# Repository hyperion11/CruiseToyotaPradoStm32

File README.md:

# CruiseToyotaPradoStm32
Cruise control for toyota prado 95
Круиз контроль для TLC Prado 95

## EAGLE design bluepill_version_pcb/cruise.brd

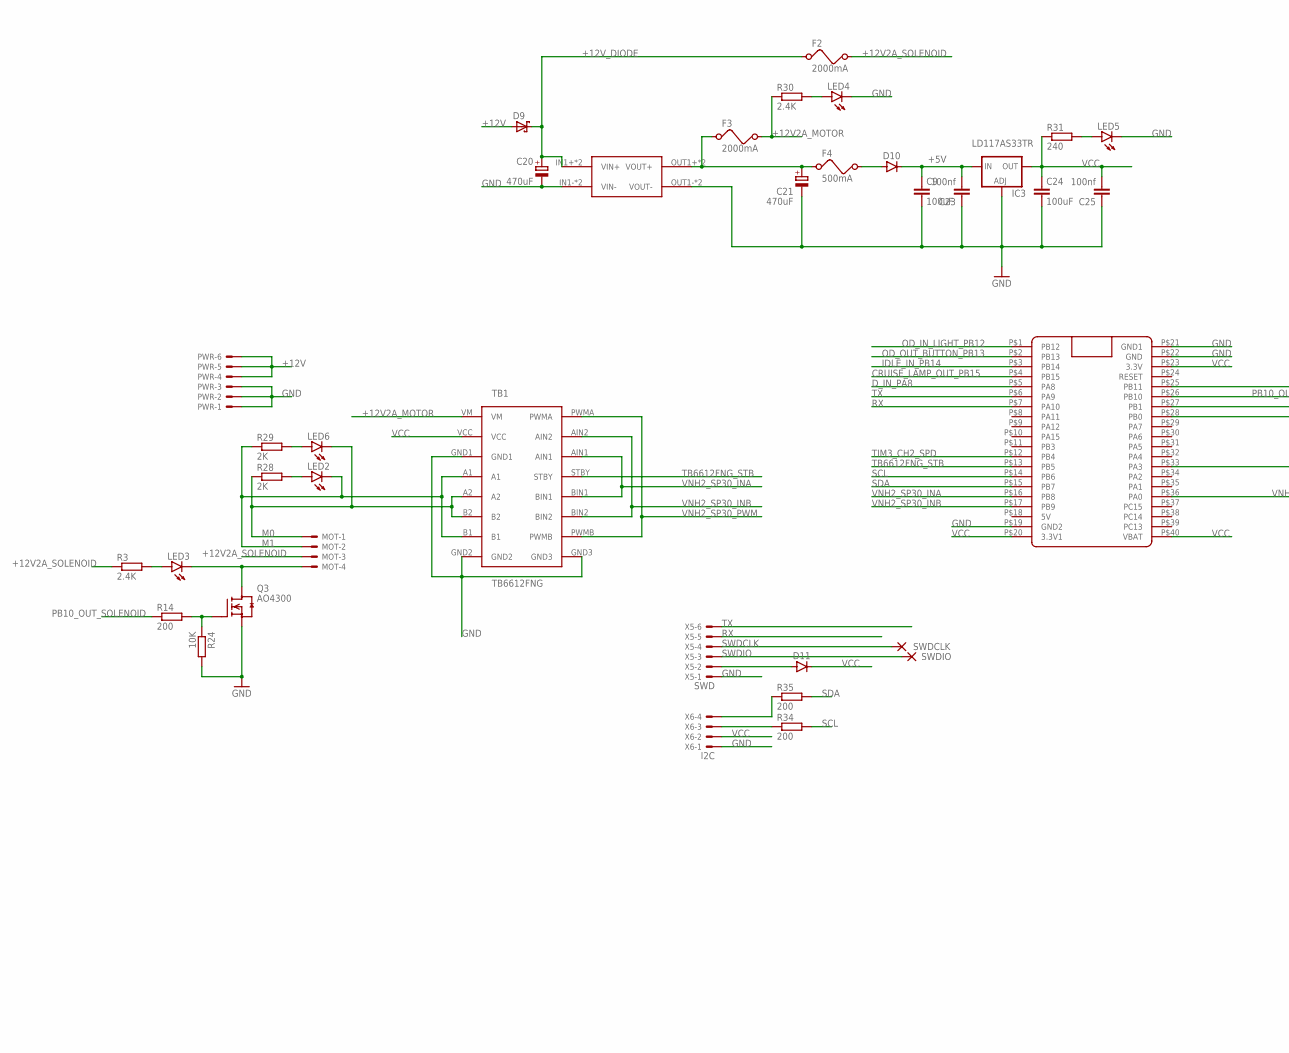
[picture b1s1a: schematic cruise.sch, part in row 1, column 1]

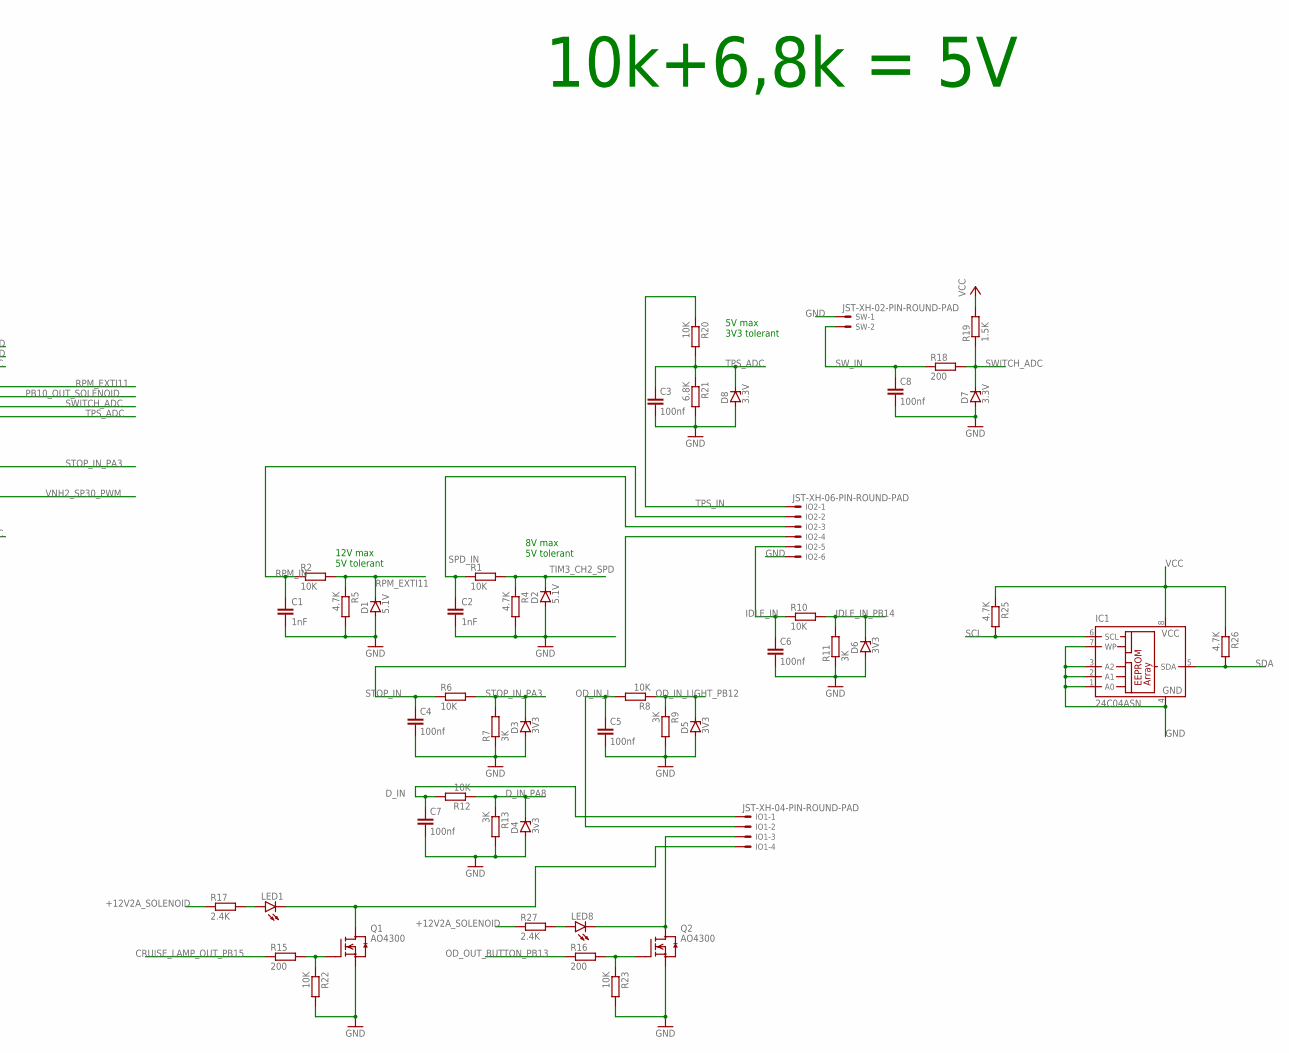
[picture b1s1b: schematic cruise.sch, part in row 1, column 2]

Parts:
C1, C2: 1nF; C0805K
C3, C4, C5, C6, C7, C8: 100nf; C0805K
C9, C24: 100uF; C1210
C20, C21: 470uF; PANASONIC_G
C23, C25: 100nf; C0805
D1, D2: 5.1V; SOD80C
D3, D5, D6: 3V3; SOD80C
D4: 3v3; SOD80C
D7, D8: 3.3V; SOD80C
D9: SCHOTTKY-DIODESMC; DIODE_SMC
D10, D11: DIODE-SOD323-W; SOD323-W
F2, F3: 2000mA; 1206
F4: 500mA; 1206
IC1: 24C04ASN; SO-08
IC3: LD117AS33TR; SOT223
IO1: JST-XH-04-PIN-ROUND-PAD; JST-XH-04-PACKAGE-ROUND-PAD
IO2: JST-XH-06-PIN-ROUND-PAD; JST-XH-06-PACKAGE-ROUND-PAD
LED1, LED2, LED3, LED4, LED5, LED6, LED8: LED3MM
MOT: JST-XH-04-PIN-LONG-PAD; JST-XH-04-PACKAGE-LONG-PAD
PWR: JST-XH-06-PIN-LONG-PAD; JST-XH-06-PACKAGE-LONG-PAD
Q1, Q2, Q3: AO4300; SOT23
R1, R2, R6, R8, R10, R12, R20, R22, R23, R24: 10K; R0805
R3, R17, R27, R30: 2.4K; R0805
R4, R5, R25, R26: 4.7K; R0805
R7, R9, R11, R13: 3K; R0805
R14, R15, R16, R18, R34, R35: 200; R0805
R19: 1.5K; R0805
R21: 6.8K; R0805
R28, R29: 2K; R0805
R31: 240; R0805
SW: JST-XH-02-PIN-ROUND-PAD; JST-XH-02-PACKAGE-ROUND-PAD
SWDCLK: WIREPAD2,15/1,0; 2,15/1,0
SWDIO: WIREPAD2,15/1,0; 2,15/1,0
TB1: TB6612FNG
U$1: BLUE_PILL
U$6: MP1584; DC-BRICK
X5: SWD; JST-XH-06-PACKAGE-ROUND-PAD
X6: I2C; JST-XH-04-PACKAGE-ROUND-PAD

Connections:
+5V: C9.1, C23.2, D10.C, IC3.3 (IN)
+12V: D9.A (C), PWR.4, PWR.5, PWR.6
+12V2A_MOTOR: F3.2, R30.1, TB1.VM
+12V2A_SOLENOID: F2.2, MOT.3, R3.1, R17.1, R27.1
+12V_DIODE: C20.+, D9.C (A), F2.1, U$6.IN1+ (VIN+), U$6.IN2+ (VIN+)
CRUISE_LAMP_OUT_PB15: R15.1, U$1.P$4 (PB15)
D_IN: C7.1, IO1.1, R12.2
D_IN_PA8: D4.C, R12.1, R13.1, U$1.P$5 (PA8)
GND: C1.2, C2.2, C3.2, C4.2, C5.2, C6.2, C7.2, C8.2, C9.2, C20.-, C21.-, C23.1, C24.2, C25.1, D1.A, D2.A, D3.A, D4.A, D5.A, D6.A, D7.A, D8.A, IC1.1 (A0), IC1.2 (A1), IC1.3 (A2), IC1.4 (GND), IC1.7 (WP), IC3.1 (ADJ), IO2.6, LED4.K (C), LED5.K (C), PWR.1, PWR.2, PWR.3, Q1.2 (S), Q2.2 (S), Q3.2 (S), R4.2, R5.2, R7.1, R9.2, R11.1, R13.2, R21.2, R22.2, R23.2, R24.2, SW.1, TB1.GND1, TB1.GND2, TB1.GND3, U$1.P$19 (GND2), U$1.P$21 (GND1), U$1.P$22 (GND), U$6.IN1- (VIN-), U$6.IN2- (VIN-), U$6.OUT1- (VOUT-), U$6.OUT2- (VOUT-), X5.1, X6.1
IDLE_IN: C6.1, IO2.5, R10.1
IDLE_IN_PB14: D6.C, R10.2, R11.2, U$1.P$3 (PB14)
M0: LED6.K (C), MOT.1, R28.1, TB1.A2, TB1.B2
M1: LED2.K (C), MOT.2, R29.1, TB1.A1, TB1.B1
unnamed: LED1.A, R17.2
unnamed: D10.A, F4.2
unnamed: D11.A, X5.2
unnamed: LED3.A, R3.2
unnamed: C21.+, F3.1, F4.1, U$6.OUT1+ (VOUT+), U$6.OUT2+ (VOUT+)
unnamed: LED3.K (C), MOT.4, Q3.3 (D)
unnamed: LED2.A, R28.2
unnamed: Q3.1 (G), R14.2, R24.1
unnamed: LED8.A, R27.2
unnamed: Q1.1 (G), R15.2, R22.1
unnamed: R34.1, X6.3
unnamed: R35.1, X6.4
unnamed: LED6.A, R29.2
unnamed: Q2.1 (G), R16.2, R23.1
unnamed: LED4.A, R30.2
unnamed: LED5.A, R31.2
unnamed: IO1.4, LED1.K (C), Q1.3 (D)
unnamed: IO1.3, LED8.K (C), Q2.3 (D)
OD_IN_L: C5.1, IO1.2, R8.2
OD_IN_LIGHT_PB12: D5.C, R8.1, R9.1, U$1.P$1 (PB12)
OD_OUT_BUTTON_PB13: R16.1, U$1.P$2 (PB13)
PB10_OUT_SOLENOID: R14.1, U$1.P$26 (PB10)
RPM_EXTI11: D1.C, R2.2, R5.1, U$1.P$25 (PB11)
RPM_IN: C1.1, IO2.2, R2.1
RX: U$1.P$7 (PA10), X5.5
SCL: IC1.6 (SCL), R25.2, R34.2, U$1.P$14 (PB6)
SDA: IC1.5 (SDA), R26.2, R35.2, U$1.P$15 (PB7)
SPD_IN: C2.1, IO2.3, R1.1
STOP_IN: C4.1, IO2.4, R6.1
STOP_IN_PA3: D3.C, R6.2, R7.2, U$1.P$33 (PA3)
SWDCLK: SWDCLK.1, X5.4
SWDIO: SWDIO.1, X5.3
SWITCH_ADC: D7.C, R18.2, R19.1, U$1.P$27 (PB1)
SW_IN: C8.1, R18.1, SW.2
TB6612FNG_STB: TB1.STBY, U$1.P$13 (PB5)
TIM3_CH2_SPD: D2.C, R1.2, R4.1, U$1.P$12 (PB4)
TPS_ADC: C3.1, D8.C, R20.2, R21.1, U$1.P$28 (PB0)
TPS_IN: IO2.1, R20.1
TX: U$1.P$6 (PA9), X5.6
VCC: C24.1, C25.2, D11.C, IC1.8 (VCC), IC3.4 (OUT), R19.2, R25.1, R26.1, R31.1, TB1.VCC, U$1.P$20 (3.3V1), U$1.P$23 (3.3V), U$1.P$40 (VBAT), X6.2
VNH2_SP30_INA: TB1.AIN1, TB1.BIN1, U$1.P$16 (PB8)
VNH2_SP30_INB: TB1.AIN2, TB1.BIN2, U$1.P$17 (PB9)
VNH2_SP30_PWM: TB1.PWMA, TB1.PWMB, U$1.P$36 (PA0)

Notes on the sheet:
10k+6,8k = 5V
8V max 5V tolerant
12V max 5V tolerant
5V max 3V3 tolerant

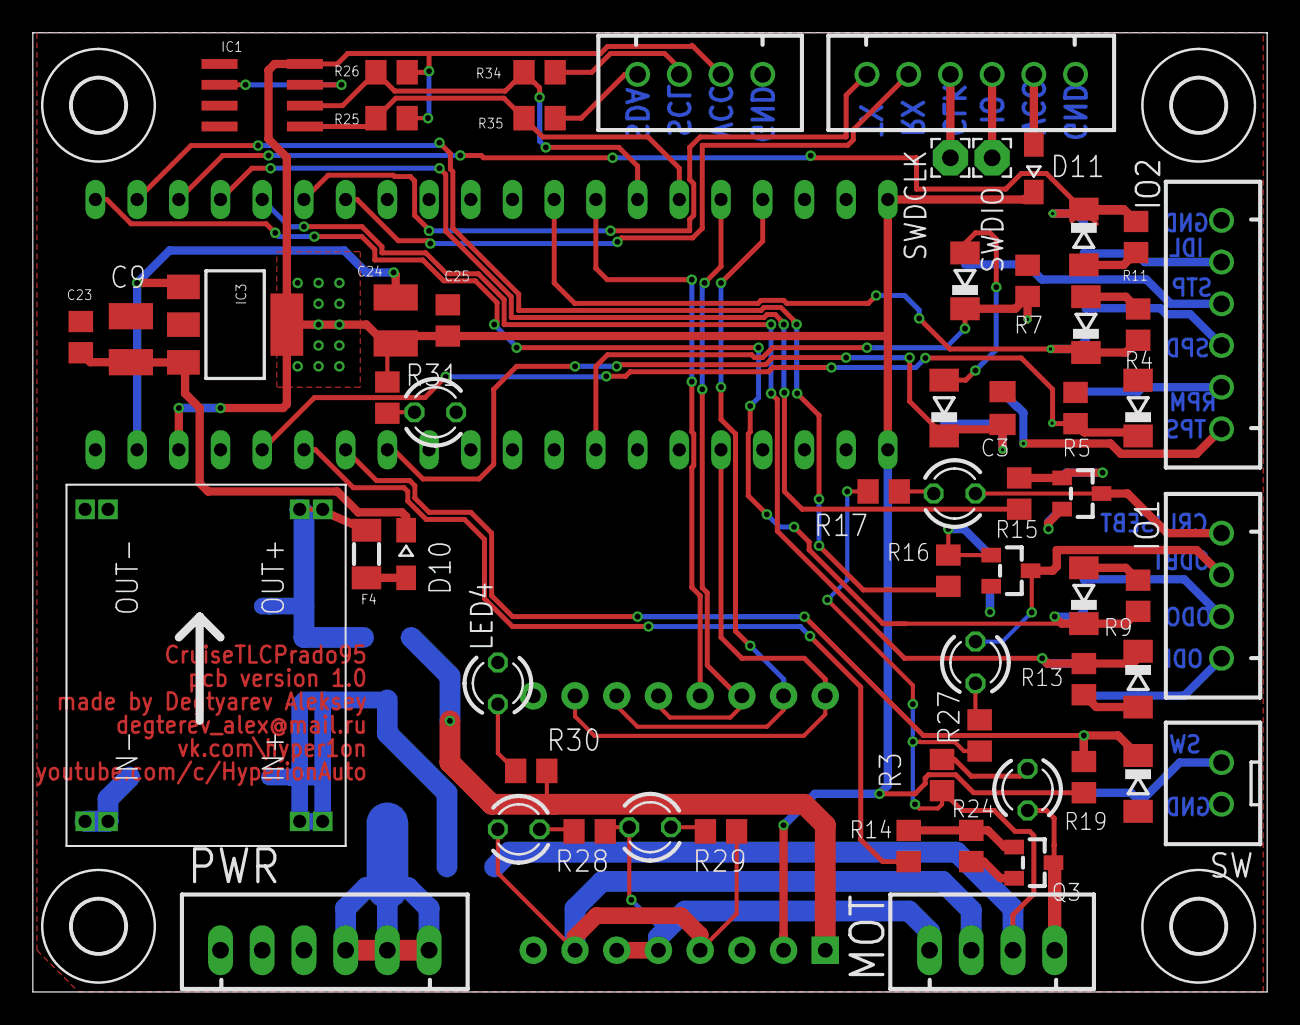
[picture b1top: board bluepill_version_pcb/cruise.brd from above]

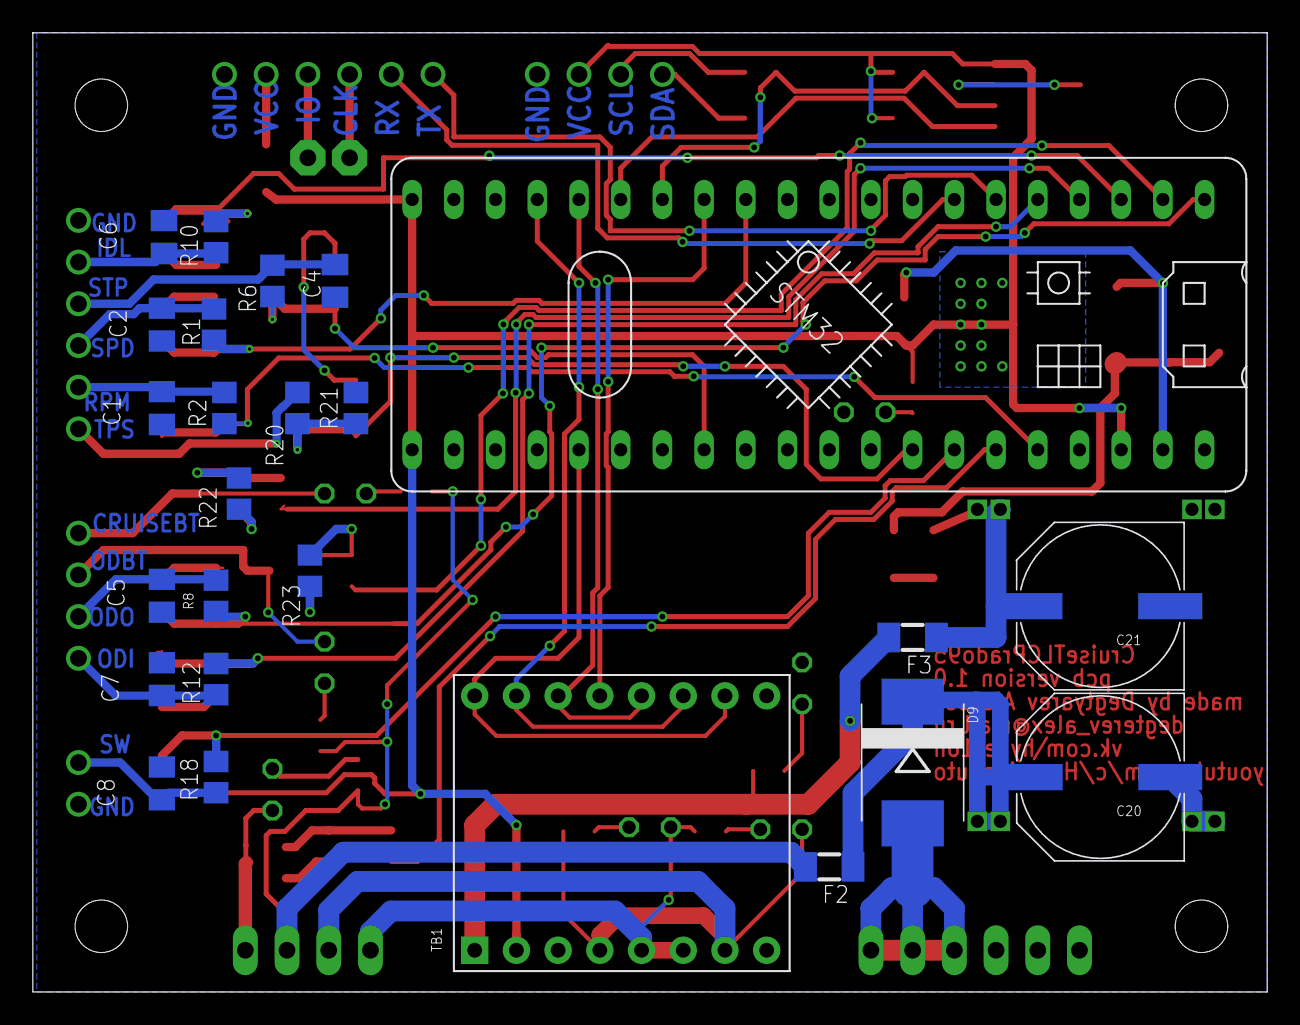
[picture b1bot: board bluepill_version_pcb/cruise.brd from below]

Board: 2 copper layers, 75.2 x 58.4 mm, 89 parts (25 on the bottom side), 56 nets.

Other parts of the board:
U$2, U$3, U$4, U$5: 3,2

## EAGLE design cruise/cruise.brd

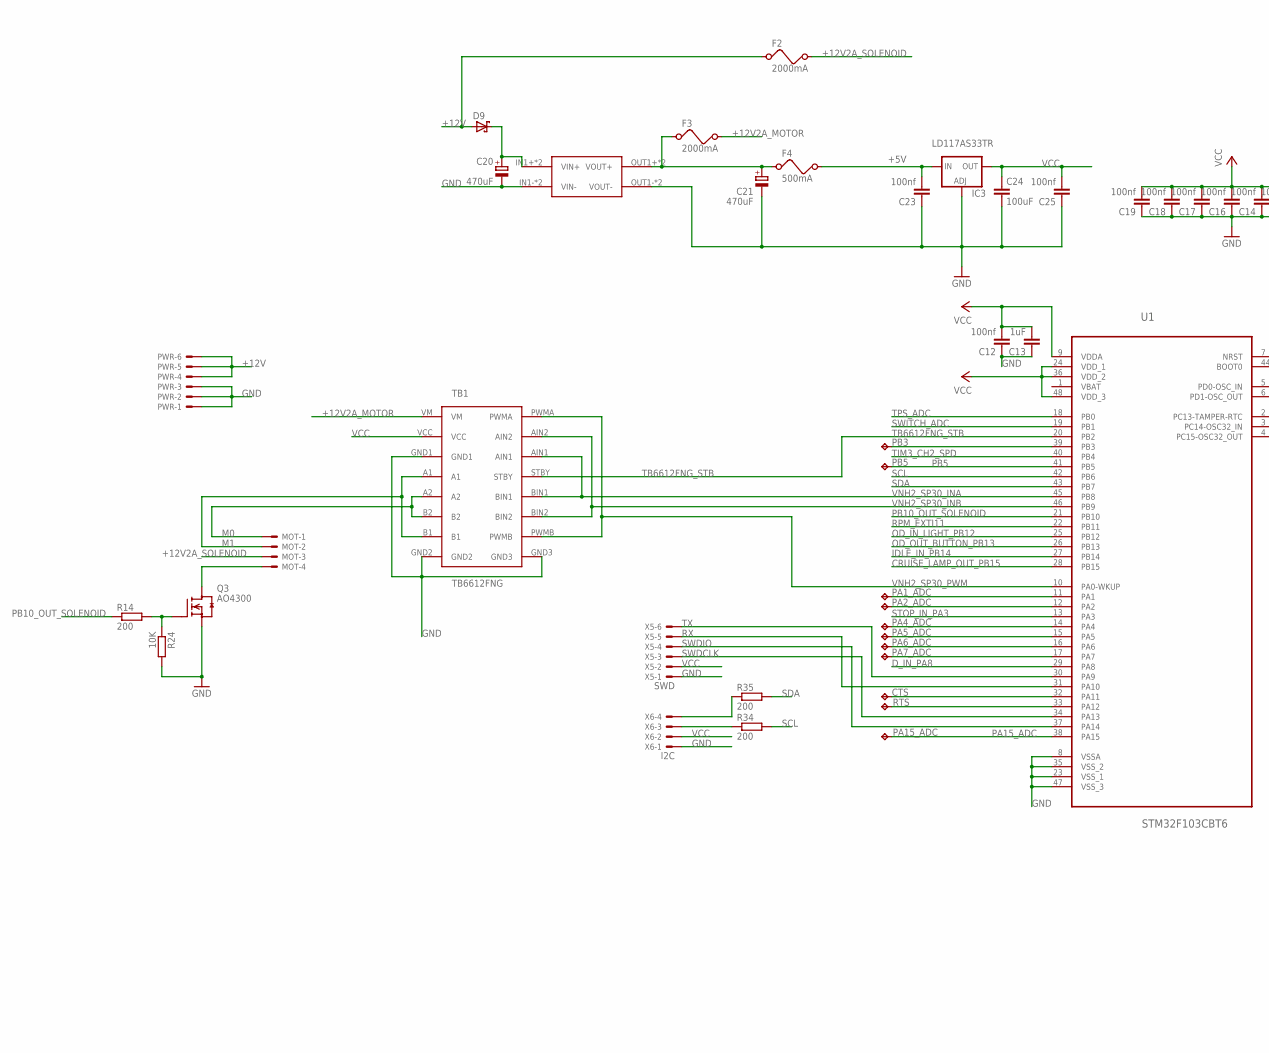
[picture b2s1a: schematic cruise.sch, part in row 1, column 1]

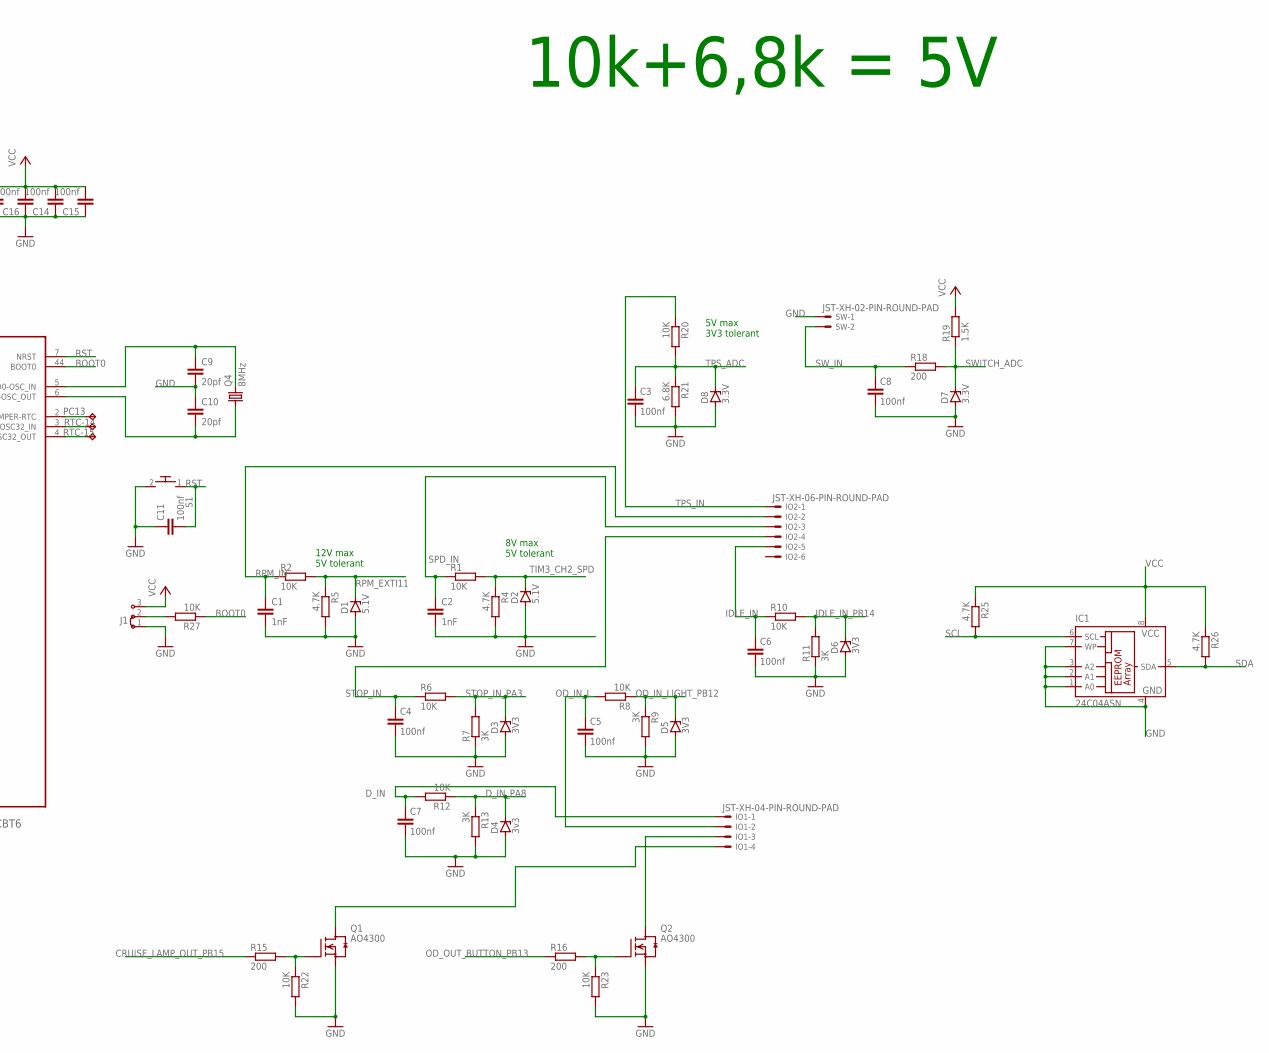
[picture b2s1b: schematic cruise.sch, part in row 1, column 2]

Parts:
C1, C2: 1nF; C0805K
C3, C4, C5, C6, C7, C8, C11, C12, C14, C15, C16, C17, C18, C19: 100nf; C0805K
C9, C10: 20pf; C0603
C13: 1uF; C0805K
C20, C21: 470uF; PANASONIC_G
C23, C25: 100nf; C0805
C24: 100uF; C1210
CTS: TPTP09R; TP09R
D1, D2: 5.1V; SOD80C
D3, D5, D6: 3V3; SOD80C
D4: 3v3; SOD80C
D7, D8: 3.3V; SOD80C
D9: SCHOTTKY-DIODESMC; DIODE_SMC
F2, F3: 2000mA; 1206
F4: 500mA; 1206
IC1: 24C04ASN; SO-08
IC3: LD117AS33TR; SOT223
IO1: JST-XH-04-PIN-ROUND-PAD; JST-XH-04-PACKAGE-ROUND-PAD
IO2: JST-XH-06-PIN-ROUND-PAD; JST-XH-06-PACKAGE-ROUND-PAD
J1: J2X2MM; 04C
MOT: JST-XH-04-PIN-LONG-PAD; JST-XH-04-PACKAGE-LONG-PAD
PA1_ADC, PA2_ADC, PA4_ADC, PA5_ADC, PA6_ADC, PA7_ADC, PA15_ADC: TPTP09R; TP09R
PB3, PB5: TPTP09R; TP09R
PC13: TPTP09R; TP09R
PWR: JST-XH-06-PIN-LONG-PAD; JST-XH-06-PACKAGE-LONG-PAD
Q1, Q2, Q3: AO4300; SOT23
Q4: 8MHz; 5.0X3.2_2
R1, R2, R6, R8, R10, R12, R20, R22, R23, R24, R27: 10K; R0805
R4, R5, R25, R26: 4.7K; R0805
R7, R9, R11, R13: 3K; R0805
R14, R15, R16, R18, R34, R35: 200; R0805
R19: 1.5K; R0805
R21: 6.8K; R0805
RTC-14, RTC-15: TPTP09R; TP09R
RTS: TPTP09R; TP09R
S1: RESET_BUTTON; EVQ-PJU05K
SW: JST-XH-02-PIN-ROUND-PAD; JST-XH-02-PACKAGE-ROUND-PAD
TB1: TB6612FNG
U1: STM32F103CBT6; QFP50P900X900X160-48N
U$6: MP1584; DC-BRICK
X5: SWD; JST-XH-06-PACKAGE-ROUND-PAD
X6: I2C; JST-XH-04-PACKAGE-ROUND-PAD

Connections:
+5V: C23.2, F4.2, IC3.3 (IN)
+12V: D9.A (C), F2.1, PWR.4, PWR.5, PWR.6
+12V2A_MOTOR: F3.2, TB1.VM
+12V2A_SOLENOID: F2.2, MOT.3
BOOT0: R27.1, U1.44 (BOOT0)
CRUISE_LAMP_OUT_PB15: R15.1, U1.28 (PB15)
D_IN: C7.1, IO1.1, R12.2
D_IN_PA8: D4.C, R12.1, R13.1, U1.29 (PA8)
GND: C1.2, C2.2, C3.2, C4.2, C5.2, C6.2, C7.2, C8.2, C9.2, C10.1, C12.1, C13.1, C14.1, C15.1, C16.1, C17.1, C18.1, C19.1, C20.-, C21.-, C23.1, C24.2, C25.1, D1.A, D2.A, D3.A, D4.A, D5.A, D6.A, D7.A, D8.A, IC1.1 (A0), IC1.2 (A1), IC1.3 (A2), IC1.4 (GND), IC1.7 (WP), IC3.1 (ADJ), J1.1, PWR.1, PWR.2, PWR.3, Q1.2 (S), Q2.2 (S), Q3.2 (S), R4.2, R5.2, R7.1, R9.2, R11.1, R13.2, R21.2, R22.2, R23.2, R24.2, SW.1, TB1.GND1, TB1.GND2, TB1.GND3, U1.8 (VSSA), U1.23 (VSS_1), U1.35 (VSS_2), U1.47 (VSS_3), U$6.IN1- (VIN-), U$6.IN2- (VIN-), U$6.OUT1- (VOUT-), U$6.OUT2- (VOUT-), X5.1, X6.1
IDLE_IN: C6.1, IO2.5, R10.1
IDLE_IN_PB14: D6.C, R10.2, R11.2, U1.27 (PB14)
M0: MOT.1, TB1.A2, TB1.B2
M1: MOT.2, TB1.A1, TB1.B1
unnamed: MOT.4, Q3.3 (D)
unnamed: C9.1, Q4.2, U1.5 (PD0-OSC_IN)
unnamed: C10.2, Q4.1, U1.6 (PD1-OSC_OUT)
unnamed: PA7_ADC.TP, U1.17 (PA7)
unnamed: C21.+, F3.1, F4.1, U$6.OUT1+ (VOUT+), U$6.OUT2+ (VOUT+)
unnamed: PB3.TP, U1.39 (PB3)
unnamed: J1.2, R27.2
unnamed: Q3.1 (G), R14.2, R24.1
unnamed: C11.1, S1.2
unnamed: Q1.1 (G), R15.2, R22.1
unnamed: R34.1, X6.3
unnamed: R35.1, X6.4
unnamed: Q2.1 (G), R16.2, R23.1
unnamed: PC13.TP, U1.2 (PC13-TAMPER-RTC)
unnamed: RTC-14.TP, U1.3 (PC14-OSC32_IN)
unnamed: RTC-15.TP, U1.4 (PC15-OSC32_OUT)
unnamed: C20.+, D9.C (A), U$6.IN1+ (VIN+), U$6.IN2+ (VIN+)
unnamed: PA1_ADC.TP, U1.11 (PA1)
unnamed: PA2_ADC.TP, U1.12 (PA2)
unnamed: PA4_ADC.TP, U1.14 (PA4)
unnamed: PA6_ADC.TP, U1.16 (PA6)
unnamed: PA5_ADC.TP, U1.15 (PA5)
unnamed: IO1.4, Q1.3 (D)
unnamed: IO1.3, Q2.3 (D)
unnamed: CTS.TP, U1.32 (PA11)
unnamed: RTS.TP, U1.33 (PA12)
OD_IN_L: C5.1, IO1.2, R8.2
OD_IN_LIGHT_PB12: D5.C, R8.1, R9.1, U1.25 (PB12)
OD_OUT_BUTTON_PB13: R16.1, U1.26 (PB13)
PA15_ADC: PA15_ADC.TP, U1.38 (PA15)
PB5: PB5.TP, U1.41 (PB5)
PB10_OUT_SOLENOID: R14.1, U1.21 (PB10)
RPM_EXTI11: D1.C, R2.2, R5.1, U1.22 (PB11)
RPM_IN: C1.1, IO2.2, R2.1
RST: C11.2, S1.1, U1.7 (NRST)
RX: U1.31 (PA10), X5.5
SCL: IC1.6 (SCL), R25.2, R34.2, U1.42 (PB6)
SDA: IC1.5 (SDA), R26.2, R35.2, U1.43 (PB7)
SPD_IN: C2.1, IO2.3, R1.1
STOP_IN: C4.1, IO2.4, R6.1
STOP_IN_PA3: D3.C, R6.2, R7.2, U1.13 (PA3)
SWDCLK: U1.37 (PA14), X5.4
SWDIO: U1.34 (PA13), X5.3
SWITCH_ADC: D7.C, R18.2, R19.1, U1.19 (PB1)
SW_IN: C8.1, R18.1, SW.2
TB6612FNG_STB: TB1.STBY, U1.20 (PB2)
TIM3_CH2_SPD: D2.C, R1.2, R4.1, U1.40 (PB4)
TPS_ADC: C3.1, D8.C, R20.2, R21.1, U1.18 (PB0)
TPS_IN: IO2.1, R20.1
TX: U1.30 (PA9), X5.6
VCC: C12.2, C13.2, C14.2, C15.2, C16.2, C17.2, C18.2, C19.2, C24.1, C25.2, IC1.8 (VCC), IC3.4 (OUT), J1.3, R19.2, R25.1, R26.1, TB1.VCC, U1.9 (VDDA), U1.24 (VDD_1), U1.36 (VDD_2), U1.48 (VDD_3), X5.2, X6.2
VNH2_SP30_INA: TB1.AIN1, TB1.BIN1, U1.45 (PB8)
VNH2_SP30_INB: TB1.AIN2, TB1.BIN2, U1.46 (PB9)
VNH2_SP30_PWM: TB1.PWMA, TB1.PWMB, U1.10 (PA0-WKUP)

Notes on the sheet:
10k+6,8k = 5V
8V max 5V tolerant
12V max 5V tolerant
5V max 3V3 tolerant

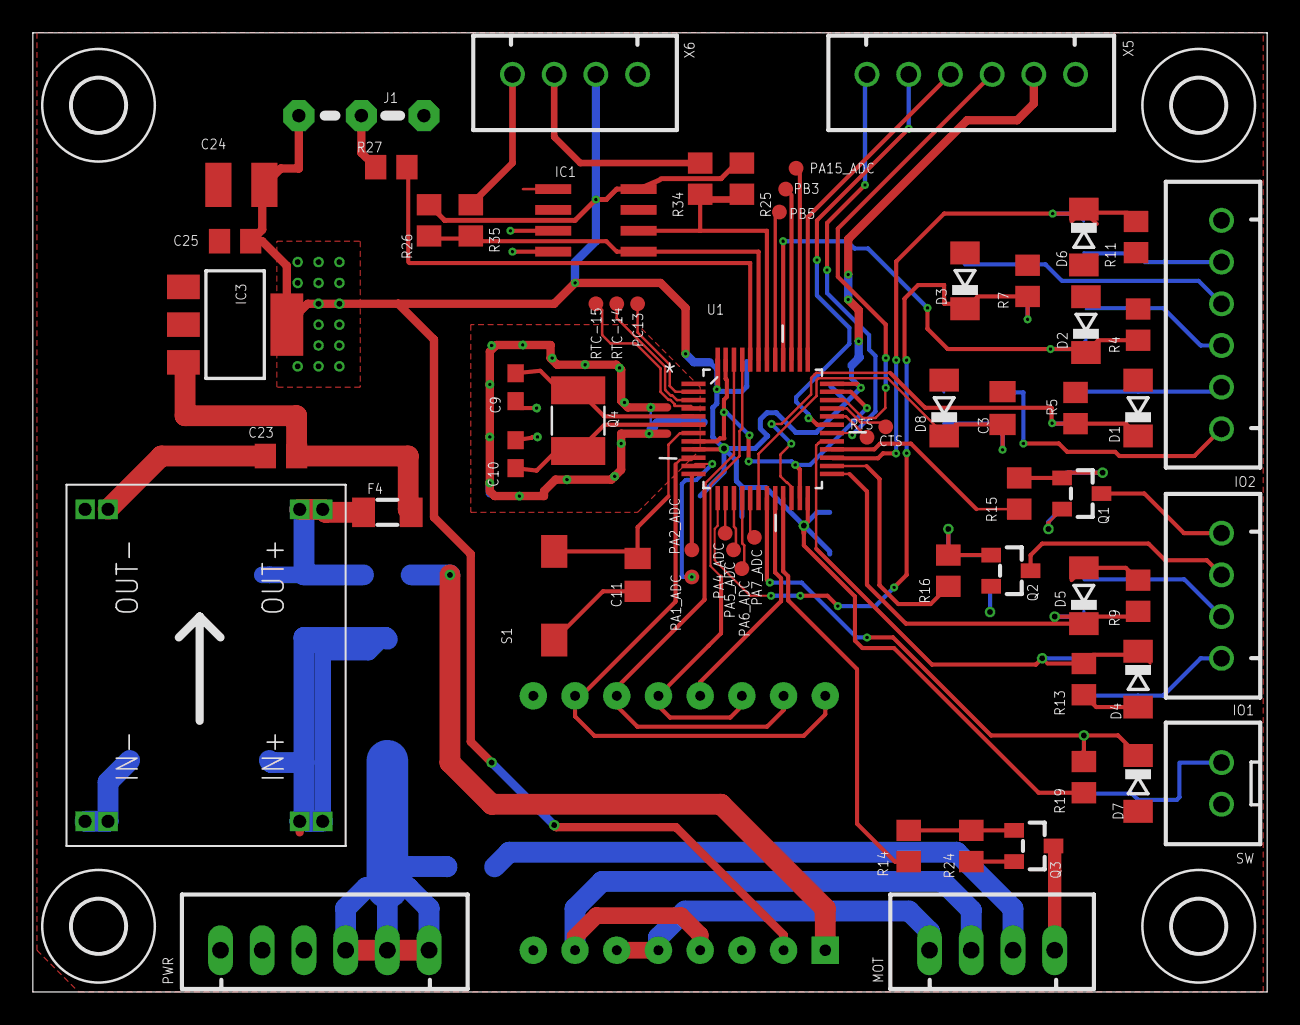
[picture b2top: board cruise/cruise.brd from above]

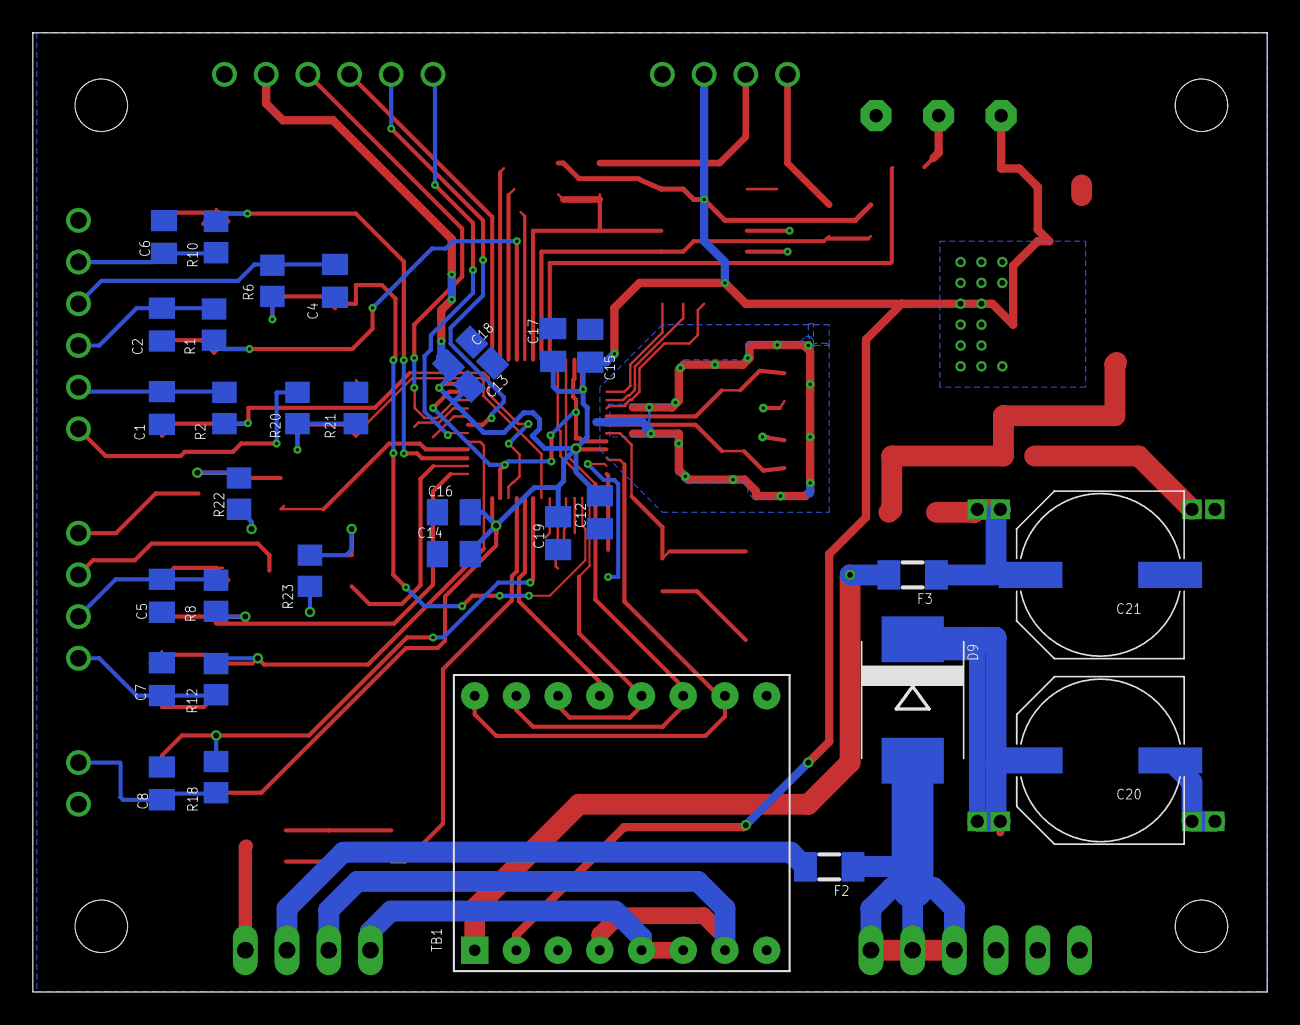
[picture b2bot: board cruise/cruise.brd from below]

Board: 2 copper layers, 75.2 x 58.4 mm, 99 parts (32 on the bottom side), 67 nets.

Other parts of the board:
U$2, U$3, U$4, U$5: 3,2

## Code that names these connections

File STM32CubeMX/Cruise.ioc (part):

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Mcu.Name=STM32F103C(8-B)Tx
Mcu.Package=LQFP48
Mcu.UserName=STM32F103C8Tx
PA0-WKUP.GPIOParameters=GPIO_Speed,GPIO_Label
PA0-WKUP.GPIO_Label=VNH2_SP30_PWM
PA0-WKUP.GPIO_Speed=GPIO_SPEED_FREQ_HIGH
PA0-WKUP.Signal=S_TIM2_CH1_ETR
PA10.Mode=Asynchronous
PA10.Signal=USART1_RX
PA13.Mode=Serial_Wire
PA13.Signal=SYS_JTMS-SWDIO
PA14.Mode=Serial_Wire
PA14.Signal=SYS_JTCK-SWCLK
PA3.GPIOParameters=GPIO_PuPd,GPIO_Label
PA3.GPIO_Label=STOP_IN_PA3
PA3.GPIO_PuPd=GPIO_PULLDOWN
PA3.Signal=GPIO_Input
PA8.GPIOParameters=GPIO_PuPd,GPIO_Label
PA8.GPIO_Label=D_IN_PA8
PA8.GPIO_PuPd=GPIO_PULLUP
PA8.Signal=GPIO_Input
PA9.Mode=Asynchronous
PA9.Signal=USART1_TX
PB0.GPIOParameters=GPIO_Label
PB0.GPIO_Label=TPS_ADC
PB0.Signal=ADCx_IN8
PB1.GPIOParameters=GPIO_Label
PB1.GPIO_Label=SWITCH_ADC
PB1.Signal=ADCx_IN9
PB10.GPIOParameters=GPIO_Label
PB10.GPIO_Label=PB10_OUT_SOLENOID
PB10.Signal=GPIO_Output
PB11.GPIOParameters=GPIO_PuPd,GPIO_Label
PB11.GPIO_Label=RPM_EXTI11
PB11.GPIO_PuPd=GPIO_PULLDOWN
PB11.Signal=GPXTI11
PB12.GPIOParameters=GPIO_PuPd,GPIO_Label
PB12.GPIO_Label=OD_IN_LIGHT_PB12
PB12.GPIO_PuPd=GPIO_PULLDOWN
PB12.Signal=GPIO_Input
PB13.GPIOParameters=GPIO_Label
PB13.GPIO_Label=OD_OUT_BUTTON_PB13
PB13.Signal=GPIO_Output
PB14.GPIOParameters=GPIO_PuPd,GPIO_Label
PB14.GPIO_Label=IDLE_IN_PB14
PB14.GPIO_PuPd=GPIO_PULLUP
PB14.Signal=GPIO_Input
PB15.GPIOParameters=GPIO_Label
PB15.GPIO_Label=CRUISE_LAMP_OUT_PB15
PB15.Signal=GPIO_Output
PB4.GPIOParameters=GPIO_Label
PB4.GPIO_Label=TIM3_CH2_SPD
PB4.Signal=S_TIM3_CH1
PB5.GPIOParameters=GPIO_PuPd,GPIO_Label
PB5.GPIO_Label=TB6612FNG_STB
PB5.GPIO_PuPd=GPIO_PULLDOWN
PB5.Signal=GPIO_Output
PB6.Mode=I2C
PB6.Signal=I2C1_SCL
PB7.Mode=I2C
PB7.Signal=I2C1_SDA
PB8.GPIOParameters=GPIO_Label
PB8.GPIO_Label=VNH2_SP30_INA
PB8.Signal=GPIO_Output
PB9.GPIOParameters=GPIO_Label
PB9.GPIO_Label=VNH2_SP30_INB
PB9.Signal=GPIO_Output
PC13-TAMPER-RTC.GPIOParameters=PinState,GPIO_Label
PC13-TAMPER-RTC.GPIO_Label=PC13
PC13-TAMPER-RTC.PinState=GPIO_PIN_SET
PC13-TAMPER-RTC.Signal=GPIO_Output
PD0-OSC_IN.Mode=HSE-External-Oscillator
PD0-OSC_IN.Signal=RCC_OSC_IN
PD1-OSC_OUT.Mode=HSE-External-Oscillator
PD1-OSC_OUT.Signal=RCC_OSC_OUT
RCC.SYSCLKFreq_VALUE=72000000
RCC.SYSCLKSource=RCC_SYSCLKSOURCE_PLLCLK
board=custom

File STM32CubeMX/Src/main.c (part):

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		duty = 0; //меньше 50 нет вращения мотора
	TIM2->CCR1 = duty;
	if (duty == 0) {
		HAL_GPIO_WritePin(VNH2_SP30_INB_GPIO_Port, VNH2_SP30_INA_Pin,
				GPIO_PIN_RESET);
		HAL_GPIO_WritePin(VNH2_SP30_INA_GPIO_Port, VNH2_SP30_INB_Pin,
				GPIO_PIN_RESET);
	} else if (dir_current == CV) {
		//пауза в случае реверса мотора
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		//	HAL_Delay(50);
	//		dir_previous = dir_current;
	//	}
		HAL_GPIO_WritePin(VNH2_SP30_INA_GPIO_Port, VNH2_SP30_INA_Pin,
				GPIO_PIN_SET);
		HAL_GPIO_WritePin(VNH2_SP30_INB_GPIO_Port, VNH2_SP30_INB_Pin,
				GPIO_PIN_RESET);
	} else if (dir_current == CCV) {
		//if (dir_current != dir_previous) {
		//	HAL_Delay(50);
		//	dir_previous = dir_current;
		//}
		HAL_GPIO_WritePin(VNH2_SP30_INA_GPIO_Port, VNH2_SP30_INA_Pin,
				GPIO_PIN_RESET);
		HAL_GPIO_WritePin(VNH2_SP30_INB_GPIO_Port, VNH2_SP30_INB_Pin,
				GPIO_PIN_SET);
	}
}
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void disarm(void) {
	CRUISE_ARMED = false;
	//отключение магнитной муфты
	HAL_GPIO_WritePin(GPIOB, PB10_OUT_SOLENOID_Pin, GPIO_PIN_RESET);
	//отключение индикатора круиза
	HAL_GPIO_WritePin(GPIOB, CRUISE_LAMP_OUT_PB15_Pin, GPIO_PIN_RESET);
	HAL_GPIO_WritePin(GPIOB, TB6612FNG_STB_Pin, GPIO_PIN_RESET);
	//останов привода круиза
	setMSpeed(0);
	arm_pid_reset_f32(&PID);
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	SPD_TARGET = (int) SPD_CURRENT + 0.1;
	CRUISE_ARMED = true;
	//включение магнитной муфты
	HAL_GPIO_WritePin(GPIOB, PB10_OUT_SOLENOID_Pin, GPIO_PIN_SET);
	//включение индикатора круиза
	HAL_GPIO_WritePin(GPIOB, CRUISE_LAMP_OUT_PB15_Pin, GPIO_PIN_SET);
	HAL_GPIO_WritePin(GPIOB, TB6612FNG_STB_Pin, GPIO_PIN_SET);
	CheckCruiseAndDisarm(STP, AT_D, IDLE, rpm, SPD_CURRENT);
}

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}

void readGPIO() {
	if (HAL_GPIO_ReadPin(GPIOA, STOP_IN_PA3_Pin) == GPIO_PIN_SET)
		//Обработка нажания на педаль тормоза. Нажата - высокий уровень. Отпущена - низкий
		STP = true;
	else
		STP = false;
	if (HAL_GPIO_ReadPin(GPIOA, D_IN_PA8_Pin) == GPIO_PIN_SET)
		//Обработка селектора АКПП. Селектор в положении D - высокий уровень. В любом другом - низкий
		AT_D = true;
	else
		AT_D = false;
	if (HAL_GPIO_ReadPin(GPIOB, IDLE_IN_PB14_Pin) == GPIO_PIN_SET)
		//Обработка ХХ. Дроссель полностью закрыт - низкий урове. Приоткрыта - высокий
		IDLE = false;
	else
		IDLE = true;

	if (HAL_GPIO_ReadPin(GPIOB, OD_IN_LIGHT_PB12_Pin) == GPIO_PIN_SET)
		//Обработка включенного OD. Нажата кнопка OD - высокий уровень. �?наче низкий
		AT_OD = true;
	else
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			screen++;
			if (screen == 2)
				screen = 0;
			HAL_GPIO_TogglePin(PC13_GPIO_Port, PC13_Pin);
		}
			break;
		case 5:       //NO PRESSED
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  __HAL_RCC_GPIOB_CLK_ENABLE();

  /*Configure GPIO pin Output Level */
  HAL_GPIO_WritePin(PC13_GPIO_Port, PC13_Pin, GPIO_PIN_SET);

  /*Configure GPIO pin Output Level */
  HAL_GPIO_WritePin(GPIOB, PB10_OUT_SOLENOID_Pin|OD_OUT_BUTTON_PB13_Pin|CRUISE_LAMP_OUT_PB15_Pin|TB6612FNG_STB_Pin 
                          |VNH2_SP30_INA_Pin|VNH2_SP30_INB_Pin, GPIO_PIN_RESET);

  /*Configure GPIO pin : PC13_Pin */
  GPIO_InitStruct.Pin = PC13_Pin;
  GPIO_InitStruct.Mode = GPIO_MODE_OUTPUT_PP;
  GPIO_InitStruct.Pull = GPIO_NOPULL;
  GPIO_InitStruct.Speed = GPIO_SPEED_FREQ_LOW;
  HAL_GPIO_Init(PC13_GPIO_Port, &GPIO_InitStruct);

  /*Configure GPIO pins : PC14 PC15 */
  GPIO_InitStruct.Pin = GPIO_PIN_14|GPIO_PIN_15;
  GPIO_InitStruct.Mode = GPIO_MODE_ANALOG;
  HAL_GPIO_Init(GPIOC, &GPIO_InitStruct);

  /*Configure GPIO pins : PA1 PA2 PA4 PA5 
                           PA6 PA7 PA9 PA10 
                           PA11 PA12 PA15 */
  GPIO_InitStruct.Pin = GPIO_PIN_1|GPIO_PIN_2|GPIO_PIN_4|GPIO_PIN_5 
                          |GPIO_PIN_6|GPIO_PIN_7|GPIO_PIN_9|GPIO_PIN_10 
                          |GPIO_PIN_11|GPIO_PIN_12|GPIO_PIN_15;
  GPIO_InitStruct.Mode = GPIO_MODE_ANALOG;
  HAL_GPIO_Init(GPIOA, &GPIO_InitStruct);

  /*Configure GPIO pin : STOP_IN_PA3_Pin */
  GPIO_InitStruct.Pin = STOP_IN_PA3_Pin;
  GPIO_InitStruct.Mode = GPIO_MODE_INPUT;
  GPIO_InitStruct.Pull = GPIO_PULLDOWN;
  HAL_GPIO_Init(STOP_IN_PA3_GPIO_Port, &GPIO_InitStruct);

  /*Configure GPIO pins : PB2 PB3 */
  GPIO_InitStruct.Pin = GPIO_PIN_2|GPIO_PIN_3;
  GPIO_InitStruct.Mode = GPIO_MODE_ANALOG;
  HAL_GPIO_Init(GPIOB, &GPIO_InitStruct);

  /*Configure GPIO pins : PB10_OUT_SOLENOID_Pin OD_OUT_BUTTON_PB13_Pin CRUISE_LAMP_OUT_PB15_Pin VNH2_SP30_INA_Pin 
                           VNH2_SP30_INB_Pin */
  GPIO_InitStruct.Pin = PB10_OUT_SOLENOID_Pin|OD_OUT_BUTTON_PB13_Pin|CRUISE_LAMP_OUT_PB15_Pin|VNH2_SP30_INA_Pin 
                          |VNH2_SP30_INB_Pin;
  GPIO_InitStruct.Mode = GPIO_MODE_OUTPUT_PP;
  GPIO_InitStruct.Pull = GPIO_NOPULL;
  GPIO_InitStruct.Speed = GPIO_SPEED_FREQ_LOW;
  HAL_GPIO_Init(GPIOB, &GPIO_InitStruct);

  /*Configure GPIO pin : RPM_EXTI11_Pin */
  GPIO_InitStruct.Pin = RPM_EXTI11_Pin;
  GPIO_InitStruct.Mode = GPIO_MODE_IT_RISING;
  GPIO_InitStruct.Pull = GPIO_PULLDOWN;
  HAL_GPIO_Init(RPM_EXTI11_GPIO_Port, &GPIO_InitStruct);

  /*Configure GPIO pin : OD_IN_LIGHT_PB12_Pin */
  GPIO_InitStruct.Pin = OD_IN_LIGHT_PB12_Pin;
  GPIO_InitStruct.Mode = GPIO_MODE_INPUT;
  GPIO_InitStruct.Pull = GPIO_PULLDOWN;
  HAL_GPIO_Init(OD_IN_LIGHT_PB12_GPIO_Port, &GPIO_InitStruct);

  /*Configure GPIO pin : IDLE_IN_PB14_Pin */
  GPIO_InitStruct.Pin = IDLE_IN_PB14_Pin;
  GPIO_InitStruct.Mode = GPIO_MODE_INPUT;
  GPIO_InitStruct.Pull = GPIO_PULLUP;
  HAL_GPIO_Init(IDLE_IN_PB14_GPIO_Port, &GPIO_InitStruct);

  /*Configure GPIO pin : D_IN_PA8_Pin */
  GPIO_InitStruct.Pin = D_IN_PA8_Pin;
  GPIO_InitStruct.Mode = GPIO_MODE_INPUT;
  GPIO_InitStruct.Pull = GPIO_PULLUP;
  HAL_GPIO_Init(D_IN_PA8_GPIO_Port, &GPIO_InitStruct);

  /*Configure GPIO pin : TB6612FNG_STB_Pin */
  GPIO_InitStruct.Pin = TB6612FNG_STB_Pin;
  GPIO_InitStruct.Mode = GPIO_MODE_OUTPUT_PP;
  GPIO_InitStruct.Pull = GPIO_PULLDOWN;
  GPIO_InitStruct.Speed = GPIO_SPEED_FREQ_LOW;
  HAL_GPIO_Init(TB6612FNG_STB_GPIO_Port, &GPIO_InitStruct);

  /* EXTI interrupt init*/
  HAL_NVIC_SetPriority(EXTI15_10_IRQn, 0, 0);
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
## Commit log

2018-12-29 попробовал добавить второй таймер
2018-12-30 move to stm32cubemx and atollic
2019-01-01 Добавлен i2c экран SSD 1306
2019-01-01 генератор -эмулятор импульсов для тахометра и спидометра добавлен
    на ардуино уно основан
2019-01-01 добавлен LCD Дисплей и генерация частот тахометра и спидометра
2019-01-02 Доделан тестовый генератор
    На экран выводится скорость, обороты.
    А также длительность импульса скорости и оборотов
2019-01-03 сделан тахометр спидометр, убрал USB
2019-01-05 Добавлен PID
2019-01-06 добавлен EEPROM 24C04
2019-01-07 начата работа над схемой
2019-01-09 ADC, arm, disarm
    Чтение 3х каналов ADC через DMA (надо проверить)
    arm, disarm круиза
2019-01-09 инжектированные каналы вместо ДМА
    + фикс багов
2019-01-10 чистка и оптимизация
2019-01-10 работа над схемой
2019-01-10 оптимизация чтения скорости
    + переделанный диагностический экран
2019-01-14 схема
2019-01-14 +pdf схема
2019-01-20 схема+проверка работы мотора
    какой то косяк с шимом. Наверное зря удалил подтягивающий резистор. Нормально работает только на частоте до 1кгц
2019-01-21 PWM+PID
    Заработал нормально Pwm 20khz
    Заработал вменяемо PID
2019-01-23 добавлен функционал тюна пидов
2019-01-23 фикс тюна пидов
2019-01-24 Управление пульсами вместо PWM.
2019-01-24 pwm
    This reverts commit 30845f196e76a9d9f96dd38ad79177a10dc0fff7.
2019-01-25 коррекция дросселя раз в 500мс
2019-01-25 усреднение скорости за 500мс перед вычислением PID
2019-01-25 чистка кода, оптимизации
2019-01-25 +constrain
2019-01-26 фиксы PID
    диапазон PID выхода от -125 до 125.
2019-02-24 измененние схемы
2019-02-25 работа со схемой
2019-02-26 еще схема
2019-04-09 drivers added
2019-04-11 rtc disable
2019-04-12 bluepill version added
2019-04-12 фикс adc
2019-05-28 перешел на PCB версию
    1. добавил задержку для инициализации экрана
    2. вернул назад таймеры для внешнего кристалла
    todo:
    проверить работу драйвера мотора. Светодиоды не светятся почему то.
2019-05-29 pinout fix
2019-05-30 rpm fix

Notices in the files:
STM32CubeMX/Src/main.c:
Copyright (c) 2018 STMicroelectronics International N.V.
All rights reserved.
(C) COPYRIGHT STMicroelectronics *****END OF FILE
parts and their libraries:
m-pad-2.1: License : GNU General Public License version 2 (see bottom)
crystal-geyer_V1_0: Copyright: Geyer-Electronic
